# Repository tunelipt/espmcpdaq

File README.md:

# espmcpdaq
Simple data acquisition system using ESP32 and MCP3208

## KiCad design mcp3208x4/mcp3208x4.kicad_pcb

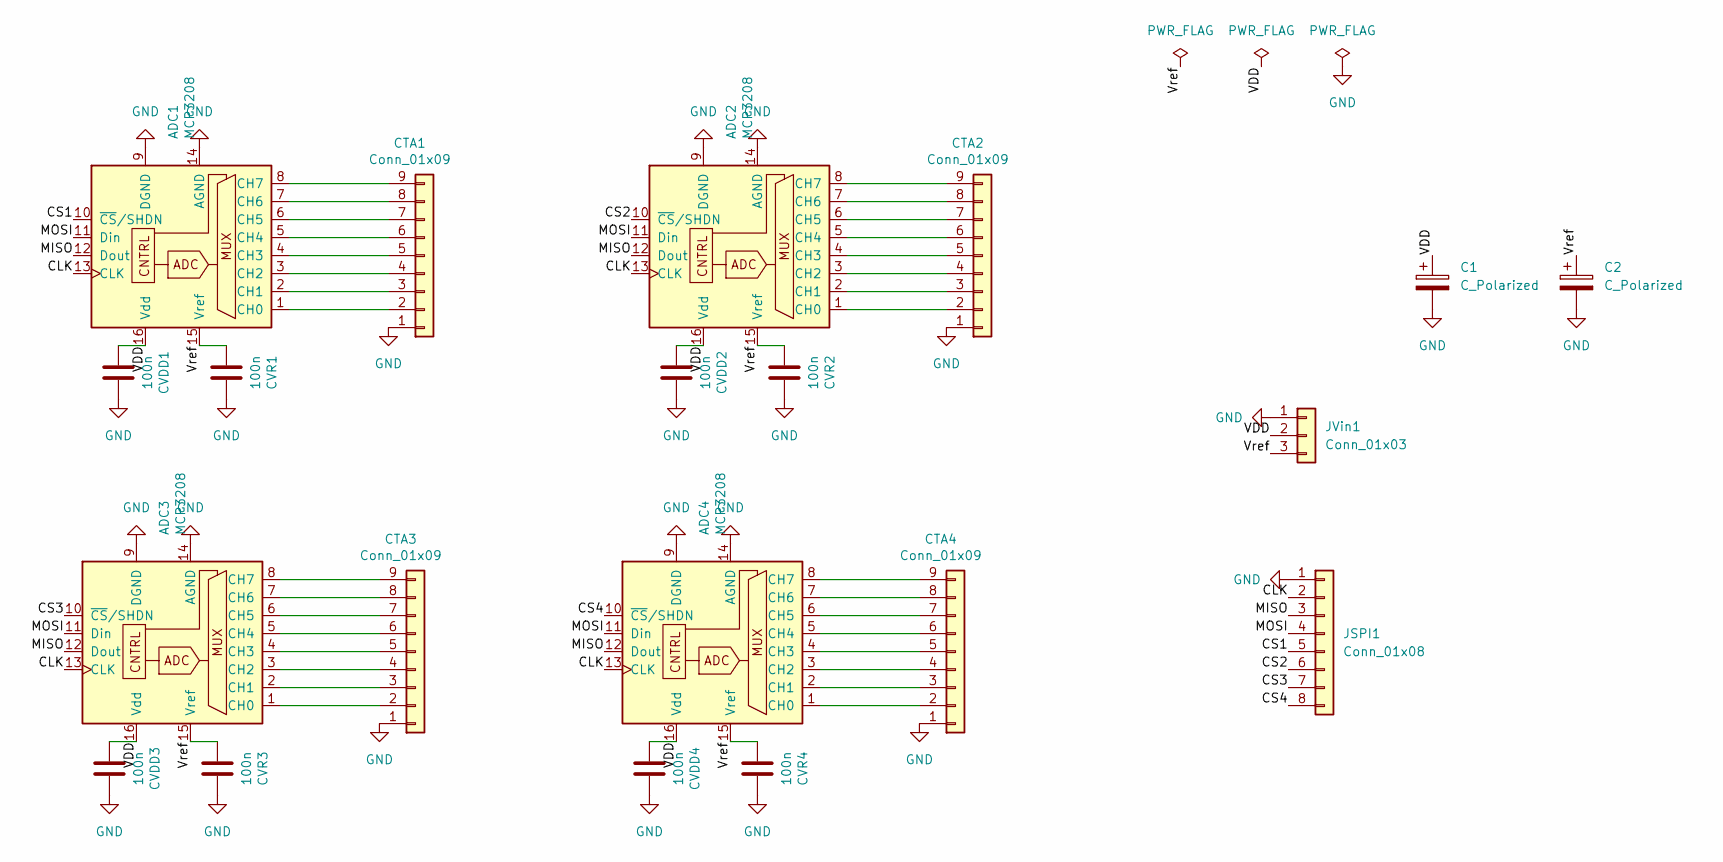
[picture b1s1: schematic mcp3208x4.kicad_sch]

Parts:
ADC1, ADC2, ADC3, ADC4: MCP3208; DIP-16_W7.62mm_LongPads
C1, C2: C_Polarized; CP_Radial_D5.0mm_P2.50mm
CTA1, CTA2, CTA3, CTA4: Conn_01x09; PinHeader_1x09_P2.54mm_Vertical
CVDD1, CVDD2, CVDD3, CVDD4: 100n; C_Rect_L7.2mm_W3.0mm_P5.00mm_FKS2_FKP2_MKS2_MKP2
CVR1, CVR2, CVR3, CVR4: 100n; C_Rect_L7.2mm_W3.0mm_P5.00mm_FKS2_FKP2_MKS2_MKP2
JSPI1: Conn_01x08; PinHeader_1x08_P2.54mm_Horizontal
JVin1: Conn_01x03; PinHeader_1x03_P2.54mm_Horizontal

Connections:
/CLK: ADC1.13 (CLK), ADC2.13 (CLK), ADC3.13 (CLK), ADC4.13 (CLK), JSPI1.2
/CS1: ADC1.10 (~CS/SHDN), JSPI1.5
/CS2: ADC2.10 (~CS/SHDN), JSPI1.6
/CS3: ADC3.10 (~CS/SHDN), JSPI1.7
/CS4: ADC4.10 (~CS/SHDN), JSPI1.8
/MISO: ADC1.12 (Dout), ADC2.12 (Dout), ADC3.12 (Dout), ADC4.12 (Dout), JSPI1.3
/MOSI: ADC1.11 (Din), ADC2.11 (Din), ADC3.11 (Din), ADC4.11 (Din), JSPI1.4
/VDD: ADC1.16 (Vdd), ADC2.16 (Vdd), ADC3.16 (Vdd), ADC4.16 (Vdd), C1.1, CVDD1.2, CVDD2.2, CVDD3.2, CVDD4.2, JVin1.2
/Vref: ADC1.15 (Vref), ADC2.15 (Vref), ADC3.15 (Vref), ADC4.15 (Vref), C2.1, CVR1.2, CVR2.2, CVR3.2, CVR4.2, JVin1.3
GND: ADC1.9 (DGND), ADC1.14 (AGND), ADC2.9 (DGND), ADC2.14 (AGND), ADC3.9 (DGND), ADC3.14 (AGND), ADC4.9 (DGND), ADC4.14 (AGND), C1.2, C2.2, CTA1.1, CTA2.1, CTA3.1, CTA4.1, CVDD1.1, CVDD2.1, CVDD3.1, CVDD4.1, CVR1.1, CVR2.1, CVR3.1, CVR4.1, JSPI1.1, JVin1.1
unnamed: ADC1.1 (CH0), CTA1.2
unnamed: ADC1.2 (CH1), CTA1.3
unnamed: ADC1.3 (CH2), CTA1.4
unnamed: ADC1.4 (CH3), CTA1.5
unnamed: ADC1.5 (CH4), CTA1.6
unnamed: ADC1.6 (CH5), CTA1.7
unnamed: ADC1.7 (CH6), CTA1.8
unnamed: ADC1.8 (CH7), CTA1.9
unnamed: ADC2.1 (CH0), CTA2.2
unnamed: ADC2.2 (CH1), CTA2.3
unnamed: ADC2.3 (CH2), CTA2.4
unnamed: ADC2.4 (CH3), CTA2.5
unnamed: ADC2.5 (CH4), CTA2.6
unnamed: ADC2.6 (CH5), CTA2.7
unnamed: ADC2.7 (CH6), CTA2.8
unnamed: ADC2.8 (CH7), CTA2.9
unnamed: ADC3.1 (CH0), CTA3.2
unnamed: ADC3.2 (CH1), CTA3.3
unnamed: ADC3.3 (CH2), CTA3.4
unnamed: ADC3.4 (CH3), CTA3.5
unnamed: ADC3.5 (CH4), CTA3.6
unnamed: ADC3.6 (CH5), CTA3.7
unnamed: ADC3.7 (CH6), CTA3.8
unnamed: ADC3.8 (CH7), CTA3.9
unnamed: ADC4.1 (CH0), CTA4.2
unnamed: ADC4.2 (CH1), CTA4.3
unnamed: ADC4.3 (CH2), CTA4.4
unnamed: ADC4.4 (CH3), CTA4.5
unnamed: ADC4.5 (CH4), CTA4.6
unnamed: ADC4.6 (CH5), CTA4.7
unnamed: ADC4.7 (CH6), CTA4.8
unnamed: ADC4.8 (CH7), CTA4.9

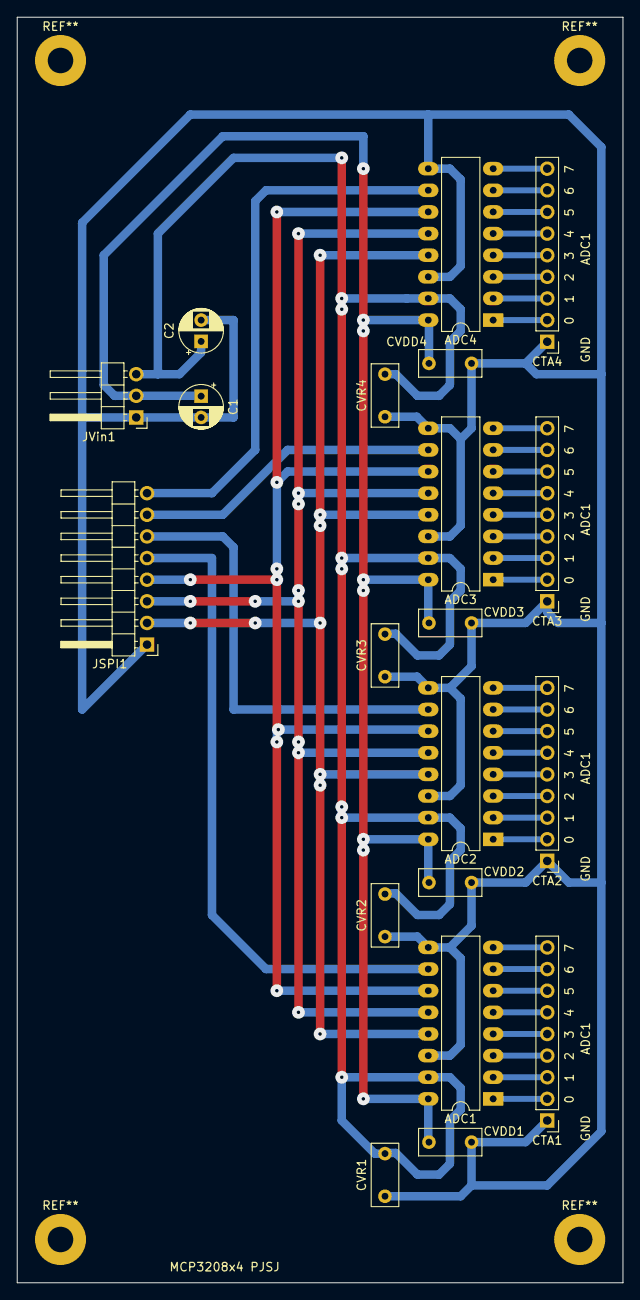
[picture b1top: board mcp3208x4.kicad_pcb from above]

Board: 2 copper layers, 71.1 x 148.6 mm, 20 parts (0 on the bottom side), 42 nets.

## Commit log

2022-06-14 Initial commit of espmcpdaq
    This is very simple ADC board developed using ESP32 and MCP3208.
    Up to 4 MCPs can be used with a total of 32 single ended channels.
    It uses LM336-2.5V as a reference voltage for ADC. This repository
    also contains the arduino files for the ESP and a python interface,
    server and client.
2022-06-14 Renamed a few of the files
    This used to be part of github.com/pjabardo/multianemdaq. Now it is independent and the file names should reflect this fact.
2022-06-14 Improved software a little bit.
    Now we can do data acquisition on the background. And we can stop the
    data acquisition.
2024-11-05 Trying to update to KiCad 8 and changing the board size
    The board should have the same size as the multianem8 board
    There are several issues with pin compatibility. I should check this
    out later...
2024-11-06 Corrected hte ERC problems.
    The issues kind of make sense. Since the same MISO and MOSI are used for every ADC, the system complains about connecting different outputs together. This not an issue because each ADC has different 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
    I still need to think about power supply for the board. The anemometers will use 24V and I could reduce this to 5V using a 78-5 or LM317 but they will run hot due to the large voltage drop. Another t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
2024-11-07 Added the possibility of choosing 5V input.
    The 5V input can come from either a terminal or the esp board USB.
    I've been thinking and I believe I should make the daq part independent
    of the board. Therefore I should deal only with SPI lines and input voltage.
2024-11-09 Just added a little text
2024-12-16 Created a board without without microcontroller or voltage reference.
    Now we can use with any microcontroller os SBC. And I can test different voltage references other than LM336.
2026-06-08 COnverted the code to PlatformIO
    I think this is easier/better than the Arduino IDE.
2026-06-09 Corrected bug when doing async daq
2026-06-12 Started to simplify the python code
    I was getting some crashes. I think I will change the approach.
2026-06-14 Working on the new python interface
    I'm trying to make everything more robust.
